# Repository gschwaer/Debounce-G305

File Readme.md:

# Deboucing Logitech G305

Searching the internet you can find several reports of Logitech G305 mice
that started to do random double clicks after a while of usage.
The problem lies in the buttons that develop a bouncy contacting behaviour.
It looks something like this:

Below you can see the signal of my mouse's left button.
It sometimes bounces even longer than 1ms (like shown here).

One way to solve this is to replace the switch with a new one.
But after some time that will also start to bounce again.

From a comment by Richard Hansen under
[a stackoverflow post](https://electronics.stackexchange.com/a/29967)
I got the idea to use the single pole double throw (SPDT) nature
of the used buttons and a Set/Reset-Latch (SR-Latch)
to defeat the problem forever.
Like this:

Which is what I did.
This is the new output signal:

Fixed. Here is what I did...

## Design

I designed a small PCB that fits into the mouse's case.
On the PCB is an SR-latch and some components to pass the signals to the mouse's controller.
First I wanted to use a dedicated SR-latch,
but I had none that supported the required 2 V supply voltage.
So I made the latch from NANDs.

I used the following parts I had at hand:
- a through-hole SN74HC00N,
- SMD (SOT-23) BSS138 n-Channel MOSFETs, and
- 1206 SMD resistors.

Since the controller seems to drive the inputs (pull-up resistors)
I am using transistors to augment a have an open drain output for the SR-latch.
This "simulates" the open and closed states of the switch for the controller
instead of driving both from the SR-latch.

(I used the pin headers only for the footprint,
I soldered the wires directly to the PCB.)

Design files are in `pcb/`. Also the gerber files in `pcb/gerber.zip`.

A similar solution was proposed [on reddit](https://www.reddit.com/r/MouseReview/comments/rx35bq/mouse_debounce_detailed_explanation/?utm_source=share&utm_medium=web2x&context=3) (contains extensive background information on the topic).

## Assembly

I am using very slim cables (0.6 mm outer diameter)
because the case is very tight in some places.

To open the case you need to peel of the glider pads on the bottom:

The PCB of the switch only exposes two pins.
The third needs to be soldered separately:

Switch pinout:
- pin on the side of the button: GND
- middle pin: pressed
- pin away from the button: unpressed

It is helpful to pull the cables from the left switch
through the end of the battery compartment (see below).
This way they will not be in the way of the LED or the DPI switch.

I found a supply voltage of 2 V at `TP11`
that is available as long as the mouse is switched on.

(I used smaller cables in the end,
because this area in the casing is very tight.
Careful not to melt the case with the soldering iron.)

I used 15 kOhm resistors that is approximately equal to the controller internal pull-ups (I measured 142 uA at 2 V).

(Note: I switched the cables on the right to slimmer ones as well.)

(The wires could be shorter. Would probably make the assembly a bit easier.)

I sealed the board in a shrink tube.
When assembling, the latch board is on the right side of the mouse.
The cables can easily be caught under the mounting posts or on the switches,
so assembling takes some time.

## Notes

- If you want to replicate this and have any questions,
  just write an issue.
- Since I use pull-up resistors also for the unpressed button state,
  the battery will probably drain faster.
  I will get back to this if it will become an issue.

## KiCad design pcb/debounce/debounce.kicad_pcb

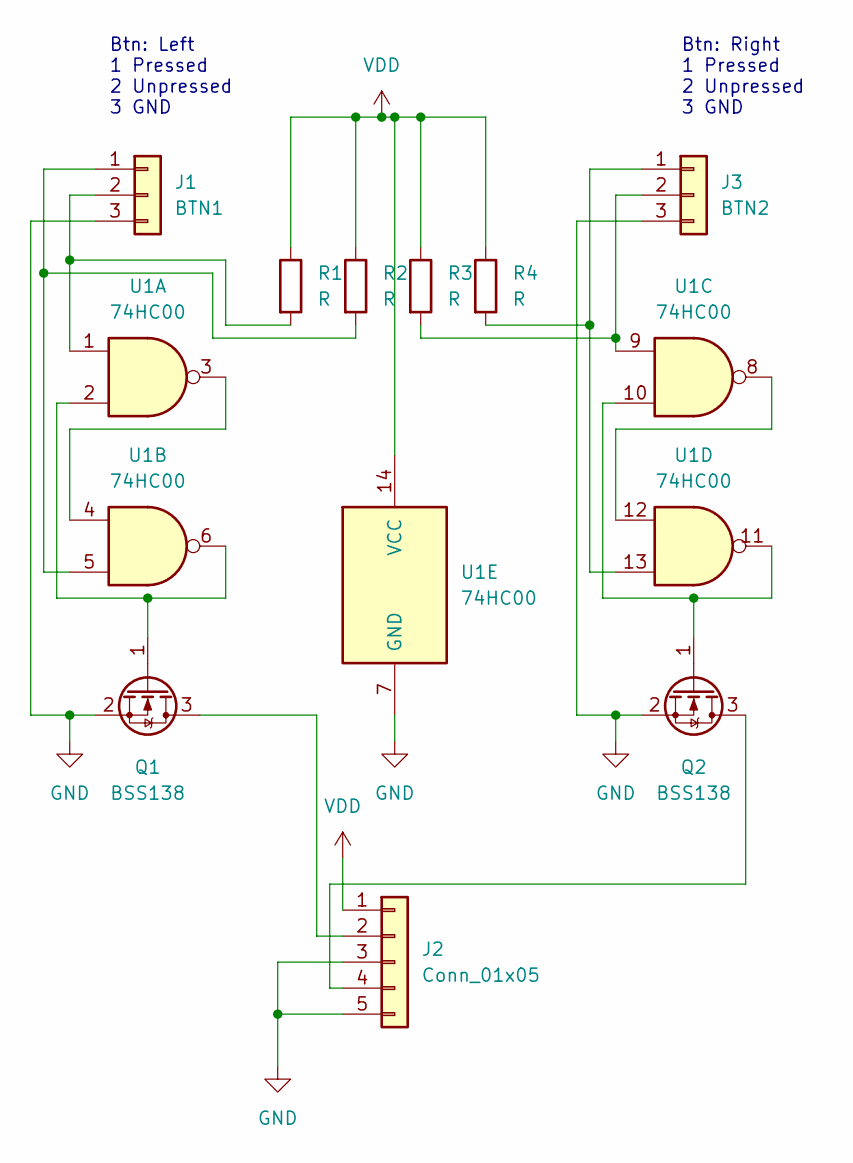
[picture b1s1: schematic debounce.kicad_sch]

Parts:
J1: BTN1; PinHeader_1x03_P2.00mm_Vertical
J2: Conn_01x05; PinHeader_1x05_P2.00mm_Vertical
J3: BTN2; PinHeader_1x03_P2.00mm_Vertical
Q1, Q2: BSS138; SOT-23
R1, R2, R3, R4: R; R_1206_3216Metric_Pad1.30x1.75mm_HandSolder
U1: 74HC00; DIP-14_W7.62mm_LongPads

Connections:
GND: J1.3, J2.3, J2.5, J3.3, Q1.2 (S), Q2.2 (S), U1.7 (GND)
unnamed: J1.1, R2.2, U1.5
unnamed: J1.2, R1.2, U1.1
unnamed: J3.1, R4.2, U1.13
unnamed: J3.2, R3.2, U1.9
unnamed: Q1.1 (G), U1.2, U1.6
unnamed: J2.2, Q1.3 (D)
unnamed: Q2.1 (G), U1.10, U1.11
unnamed: J2.4, Q2.3 (D)
unnamed: U1.3, U1.4
unnamed: U1.8, U1.12
VDD: J2.1, R1.1, R2.1, R3.1, R4.1, U1.14 (VCC)

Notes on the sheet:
Btn: Right 1 Pressed 2 Unpressed 3 GND
Btn: Left 1 Pressed 2 Unpressed 3 GND

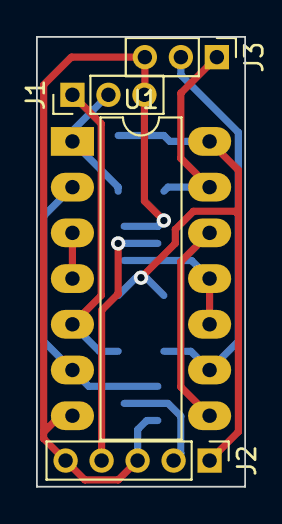
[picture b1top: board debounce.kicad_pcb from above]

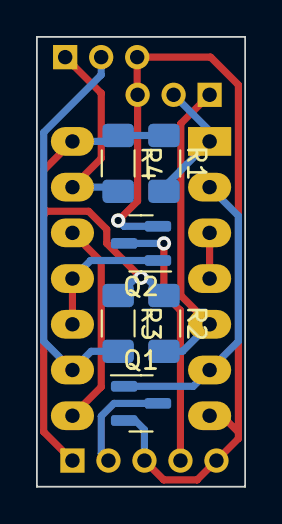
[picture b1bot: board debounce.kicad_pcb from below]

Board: 2 copper layers, 11.6 x 25.0 mm, 10 parts (6 on the bottom side), 12 nets.
